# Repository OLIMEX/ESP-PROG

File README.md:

# ESP-PROG
ESP-PROG is USB programmer for ESP8266 and ESP32.

Product page: https://www.olimex.com/Products/IoT/Programmer/ESP-PROG/open-source-hardware

## Licensee
* Hardware is released under CERN Open Hardware Licence Version 2 -
Strongly Reciprocal
* Software is released under GPL3 Licensee
* Documentation is released under CC BY-SA 3.0

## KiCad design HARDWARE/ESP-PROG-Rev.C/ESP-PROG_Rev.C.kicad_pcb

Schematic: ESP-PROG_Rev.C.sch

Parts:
C1, C3: 2.2uF; C_0603_5MIL_DWS
C2, C4: 27pF; C_0402_5MIL_DWS
CON1: CON6; WU06SM
CON2: CON6; HN1x6
Q1, Q2: BC817-40(SOT23); SOT23
R1, R2: 1K; R_0402_5MIL_DWS
R3, R4: 100R; R_0402_5MIL_DWS
U1: CH340H/T; SSOP-20W
U2: ME6210-SOT89; SOT89
USB1: USB-uicro-B; USB-MICRO_MISB-SWMM-5B_LF
Y1: Q12MHz/20pF/10ppm/4P/3.2x2.5mm; TSX-3.2x2.5mm_GND(3)

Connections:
/+3.3V: C3.1, CON1.5, CON2.5, U1.5 (V3), U1.19 (VCC), U2.3
/DCOM: CON1.2, CON2.2, Q1.3
/DTR: Q1.2, R2.2, U1.15 (DTR#)
/D_N: U1.7 (UD-), USB1.2 (D-)
/D_P: U1.6 (UD+), USB1.3 (D+)
/EN: CON1.6, CON2.6, Q2.3
/RTS: Q2.2, R1.2, U1.16 (RTS#)
/U0RXD: CON1.3, CON2.3, R3.1
/U0TXD: CON1.1, CON2.1, R4.1
GND: C1.2, C2.2, C3.2, C4.2, CON1.4, CON2.4, U1.8 (GND), U2.1, USB1.0, USB1.5 (GND), Y1.3
unnamed: C1.1, CON2.7, U2.2, USB1.1 (VBUS)
unnamed: C2.1, U1.10 (XO), Y1.2
unnamed: C4.1, U1.9 (XI), Y1.1
unnamed: Q1.1, R1.1
unnamed: Q2.1, R2.1
unnamed: R3.2, U1.3 (TXD)
unnamed: R4.2, U1.4 (RXD)

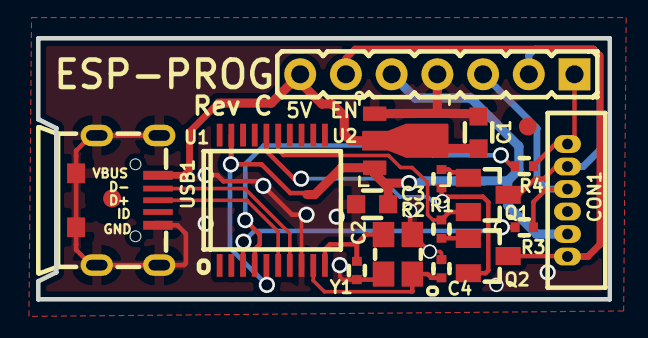
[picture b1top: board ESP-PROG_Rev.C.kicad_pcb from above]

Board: 2 copper layers, 31.8 x 14.5 mm, 18 parts (0 on the bottom side), 17 nets.

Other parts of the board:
Ref*: Val**; Fiducial1x3_transp
Ref*#2: Val**; Fiducial1x3_transp

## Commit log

2020-05-27 initial upload

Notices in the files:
HARDWARE/ESP-PROG-Rev.C/ESP-PROG_Rev.C.kicad_pcb:
(c) 2020
